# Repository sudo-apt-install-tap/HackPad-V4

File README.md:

<div align="center">

<h1>
  <b>
    HackPad v4
  </b> 
</h1>

<h3> <b> A 9 Keys, Per-Key RGB with a 0.91" OLED Macropad! </b> </h3>

</div>

## **Overview**

A Macropad With **8** Keys addressable per key RGB and an OLED module

### Why?

My old macropad doesn't get used that often and I cant keep track of all the 16 keys. Thus this will be a more compact build for me and hopefully I will be able to integrate this fully into my system.

also because SCREEN WITH CLIKIES

### How?
Use the firmware in [FIRMWARE](firmware) . This is my first time using QMK and I'm proud of my work because this is much more efficient than circuitpy running KMK.

## CAD
CAD files are available at [CAD](https://cad.onshape.com/documents/d76080119db72d3389085b9f/w/6c29cdd82ab150742e4f6482/e/dc89bac09447832fc9f2681d?renderMode=0&uiState=6acbcdec1bb4641ff654fc3b)

## Images
<div align="center">

<br> Full render<br>

---

<br> PCB

---

<br> Sch

---

<br> 3D Viewer

---

</div>

## BOM

| Part | What it's for | Qty | Unit | Total | Vendor |
| --- | --- | --- | --- | --- | --- |
| [PCB](https://jlcpcb.com/) | Printed circuit board | 1 | $5.00 | $5.00 | [JLCPCB](https://jlcpcb.com/) |
| [Gateron Milky PRO Switch – 5pin](https://meckeys.com/shop/accessories/keyboard-accessories/key-switches/gateron-mechanical-pro-switch-5pin/?attribute_pa_gateron-key-switches=pro-milky-yellow) | Switches that THOCC | 1 | $2.50 | $2.50 | [MecKeys](https://meckeys.com/shop/accessories/keyboard-accessories/key-switches/gateron-mechanical-pro-switch-5pin/?attribute_pa_gateron-key-switches=pro-milky-yellow) |
| [Blank DSA Keycaps (1u) [Pack of 5]](https://meckeys.com/shop/accessories/keyboard-accessories/keycaps/blank/blank-dsa-keycaps-1u/?attribute_pa_keycap-theme=black) | Keycaps | 2 | $1.25 | $2.50 | [MecKeys](https://meckeys.com/shop/accessories/keyboard-accessories/keycaps/blank/blank-dsa-keycaps-1u/?attribute_pa_keycap-theme=black) |
| [Seeed Studio XIAO RP2040 v1.0](https://robu.in/product/seeed-studio-xiao-rp2040-v1-0/) | MCU | 1 | $6.00 | $6.00 | [Robu.in](https://robu.in/product/seeed-studio-xiao-rp2040-v1-0/) |
| [0.91 inch 128x32 Blue OLED Display Module with I2C/IIC Serial Interface](https://robu.in/product/blue-oled-display-module/) | 2.32cm(0.91inch) I2C/IIC Blue Color OLED Display Module offers 128×32 pixel resolution. | 1 | $2.00 | $2.00 | [Robu.in](https://robu.in/product/blue-oled-display-module/) |
| [1N4148W-7-F-Diodes Incorporated-100V Independent Type 1.25V@150mA 4ns 300mA SOD-123 Switching Diodes ROHS](https://robu.in/product/1n4148w-7-f-diodes-incorporated-100v-independent-type-1-25v150ma-4ns-300ma-sod-123-switching-diodes-rohs/) | Diodes | 20 | $0.03 | $0.60 | [Robu.in](https://robu.in/product/1n4148w-7-f-diodes-incorporated-100v-independent-type-1-25v150ma-4ns-300ma-sod-123-switching-diodes-rohs/) |
| [sk6812 mini-e](https://robu.in/product/1n4148w-7-f-diodes-incorporated-100v-independent-type-1-25v150ma-4ns-300ma-sod-123-switching-diodes-rohs/) | Backlight | 9 | $0.00 | $0.00 | [self sourced](https://robu.in/product/1n4148w-7-f-diodes-incorporated-100v-independent-type-1-25v150ma-4ns-300ma-sod-123-switching-diodes-rohs/) |
| [Print legion](https://hackclub.slack.com/archives/C083P4FJM46/p1791742458204589) | Case 3d printing | 1 | $6.40 | $6.40 | [Print Legion](https://hackclub.slack.com/archives/C083P4FJM46/p1791742458204589) |
| **Parts subtotal** | — | — | — | **$25.00** | — |
| **Tax & shipping** | — | — | — | **$5.00** | — |
| **Total** | — | — | — | **$30.00** | — |

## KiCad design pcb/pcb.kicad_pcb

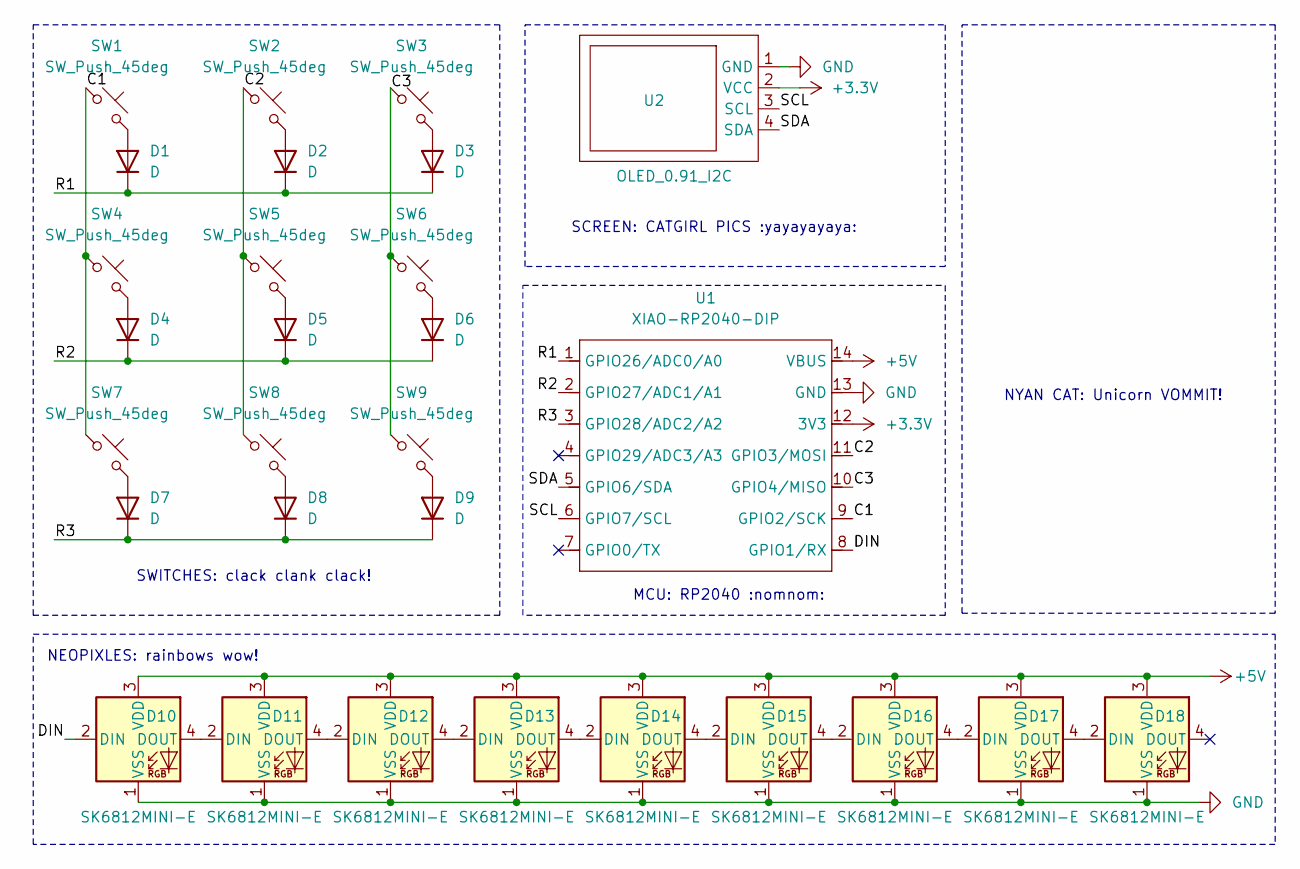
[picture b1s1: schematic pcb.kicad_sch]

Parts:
D1, D2, D3, D4, D5, D6, D7, D8, D9: D; D_SOD-123
D10, D11, D12, D13, D14, D15, D16, D17, D18: SK6812MINI-E; MX_SK6812MINI-E
SW1, SW2, SW3, SW4, SW5, SW6, SW7, SW8, SW9: SW_Push_45deg; SW_Cherry_MX_PCB
U1: XIAO-RP2040-DIP; XIAO-RP2040-SMD
U2: OLED_0.91_I2C; PinSocket_1x04_P2.54mm_Vertical

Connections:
+3.3V: U1.12 (3V3), U2.2 (VCC)
+5V: D10.3 (VDD), D11.3 (VDD), D12.3 (VDD), D13.3 (VDD), D14.3 (VDD), D15.3 (VDD), D16.3 (VDD), D17.3 (VDD), D18.3 (VDD), U1.14 (VBUS)
/C1: SW1.1, SW4.1, SW7.1, U1.9 (GPIO2/SCK)
/C2: SW2.1, SW5.1, SW8.1, U1.11 (GPIO3/MOSI)
/C3: SW3.1, SW6.1, SW9.1, U1.10 (GPIO4/MISO)
/DIN: D10.2 (DIN), U1.8 (GPIO1/RX)
/R1: D1.1 (K), D2.1 (K), D3.1 (K), U1.1 (GPIO26/ADC0/A0)
/R2: D4.1 (K), D5.1 (K), D6.1 (K), U1.2 (GPIO27/ADC1/A1)
/R3: D7.1 (K), D8.1 (K), D9.1 (K), U1.3 (GPIO28/ADC2/A2)
/SCL: U1.6 (GPIO7/SCL), U2.3 (SCL)
/SDA: U1.5 (GPIO6/SDA), U2.4 (SDA)
GND: D10.1 (VSS), D11.1 (VSS), D12.1 (VSS), D13.1 (VSS), D14.1 (VSS), D15.1 (VSS), D16.1 (VSS), D17.1 (VSS), D18.1 (VSS), U1.13 (GND), U2.1 (GND)
unnamed: D1.2 (A), SW1.2
unnamed: D2.2 (A), SW2.2
unnamed: D3.2 (A), SW3.2
unnamed: D4.2 (A), SW4.2
unnamed: D5.2 (A), SW5.2
unnamed: D6.2 (A), SW6.2
unnamed: D7.2 (A), SW7.2
unnamed: D8.2 (A), SW8.2
unnamed: D9.2 (A), SW9.2
unnamed: D10.4 (DOUT), D11.2 (DIN)
unnamed: D11.4 (DOUT), D12.2 (DIN)
unnamed: D12.4 (DOUT), D13.2 (DIN)
unnamed: D13.4 (DOUT), D14.2 (DIN)
unnamed: D14.4 (DOUT), D15.2 (DIN)
unnamed: D15.4 (DOUT), D16.2 (DIN)
unnamed: D16.4 (DOUT), D17.2 (DIN)
unnamed: D17.4 (DOUT), D18.2 (DIN)

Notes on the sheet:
NYAN CAT: Unicorn VOMMIT!
SWITCHES: clack clank clack!
SCREEN: CATGIRL PICS :yayayayaya:
NEOPIXLES: rainbows wow!
MCU: RP2040 :nomnom:

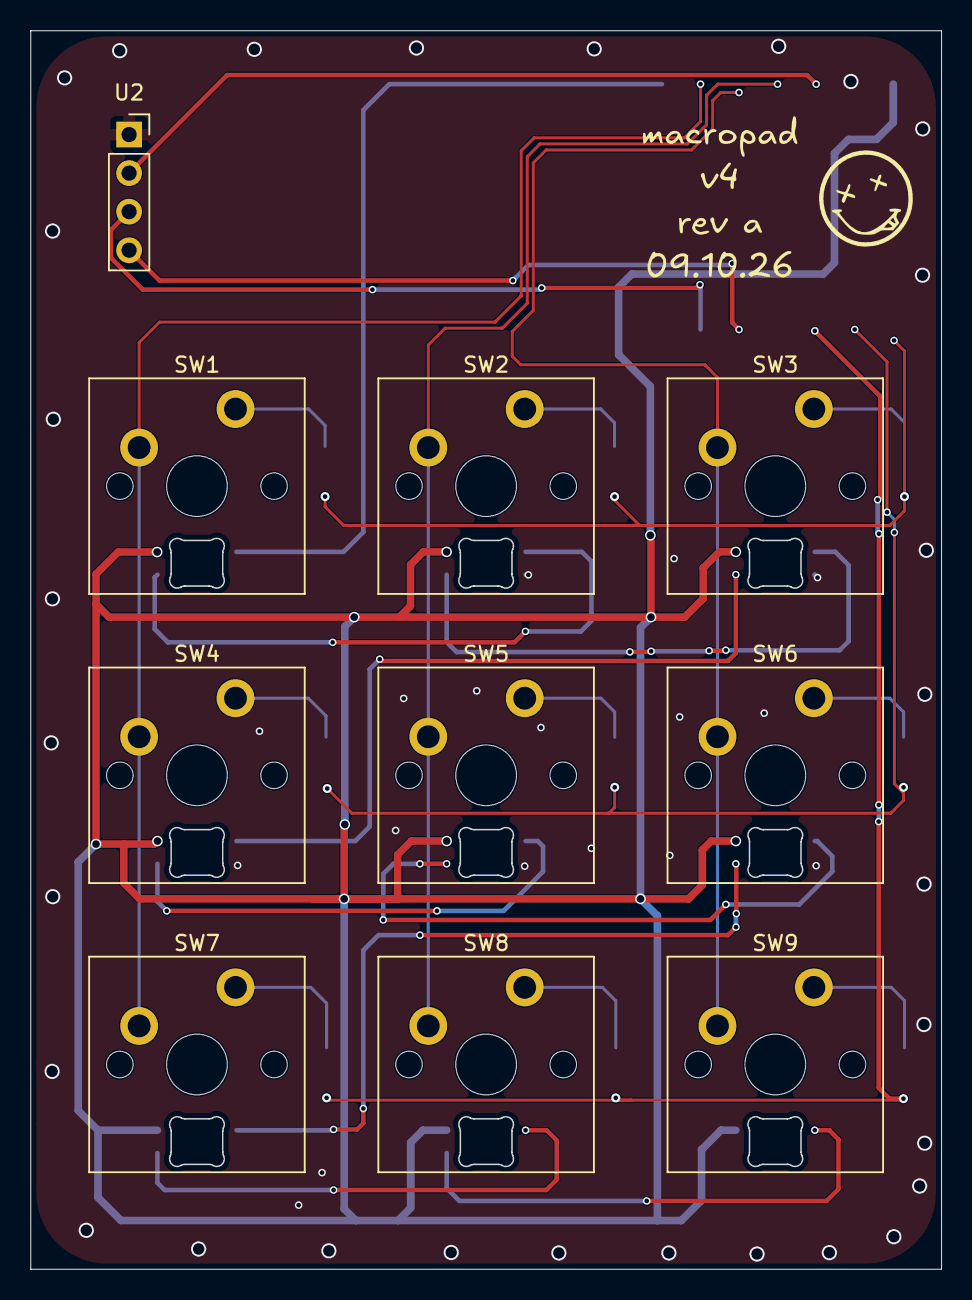
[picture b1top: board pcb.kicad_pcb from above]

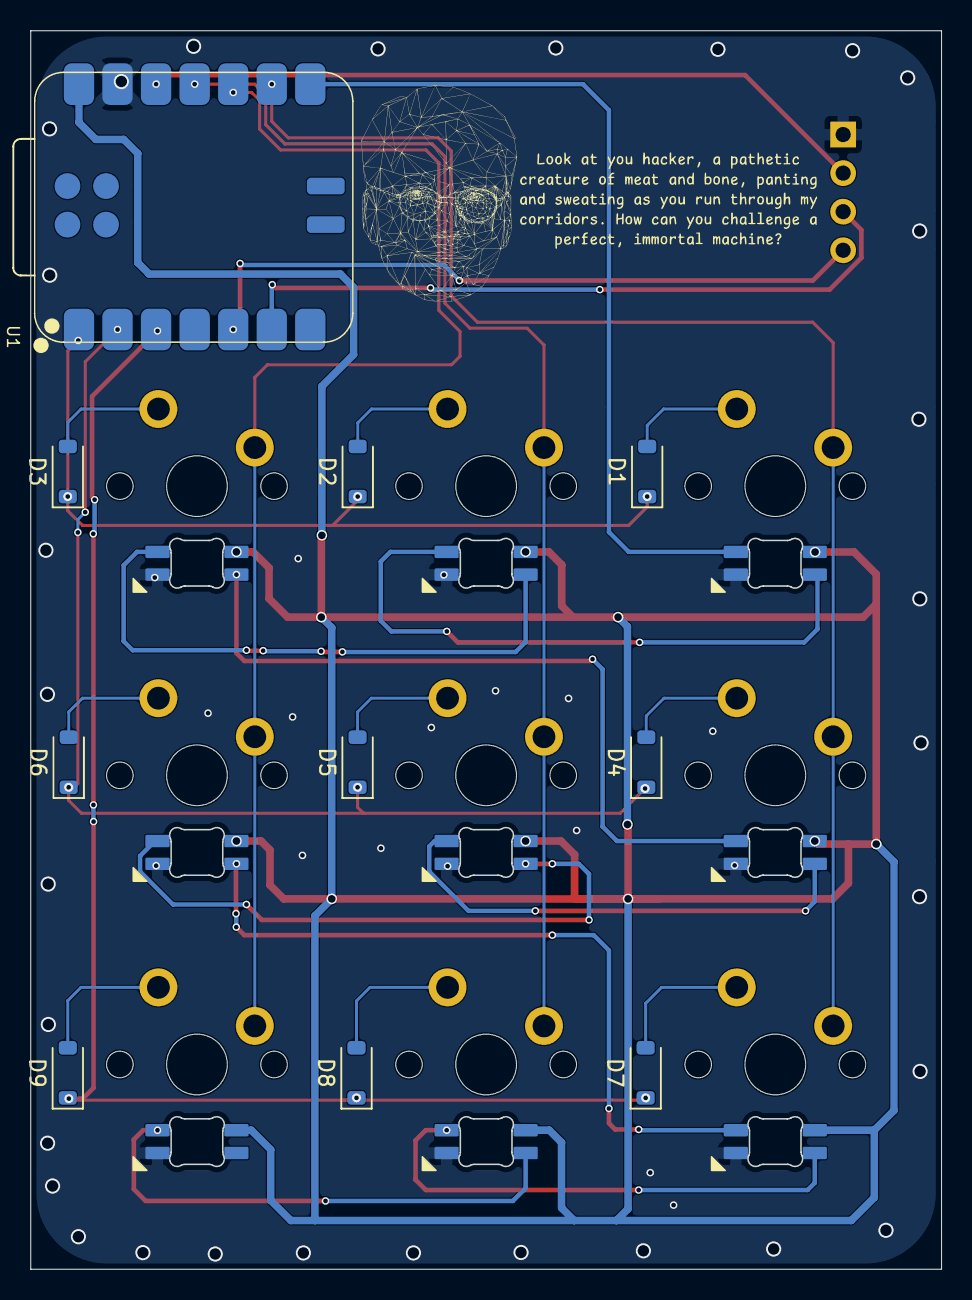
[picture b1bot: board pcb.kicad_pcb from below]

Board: 2 copper layers, 60.0 x 81.6 mm, 29 parts (10 on the bottom side), 29 nets.

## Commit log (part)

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2026-06-07 Add initial README for HackPad V4
2026-06-15 Finished PCB
2026-06-15 Add journal entry for completed PCB project
    Documented completion of PCB project using KiCAD10 with images.
